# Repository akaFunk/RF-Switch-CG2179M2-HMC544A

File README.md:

# RF Switch CG2179M2 or HMC544A
This PCB can hold either the CEL CG2179M2 [1] or the Analog Devices (former Hitite) HMC544A [2] which are both medium power reflective RF switches (31 and 39 dBm, respectively). The frequency range is DC to 3 GHz or DC to 4 GHz, respectively.

The PCB has a height of 0.6 mm, which is crucial (at least at higher frequencies) and it was ordered in China [3]. The populated PCB was soldered into a tinplate filter housing FG1 of size 37x20x20 mm [4]. To get the control voltages into the housing two 1000 pF feed through capacitor DF 38 [5] were used.

If you wish to use the switch for fast switching you should not populate the two capacitors C4 and C5. Additionally C1, C2 and C3 may be increased for frequencies lower than 100 MHz and decreased for frequencies above 500 MHz. Use proper high frequency capacitors. If DC signal is required, the capacitors C1, C2 and C3 must be replaced by a short or 0 Ohm resistor.

## Images

## References
[1] http://www.cel.com/parts.do?command=load&idRootPart=2604  
[2] http://www.analog.com/en/products/rf-microwave/rf-switches/spdt-t-r/hmc544a.html  
[3] http://www.elecrow.com  
[4] http://www.schubert-gehaeuse.de/prod01.htm  
[5] http://www.oppermann-electronic.de/html/durchf__c_s.html

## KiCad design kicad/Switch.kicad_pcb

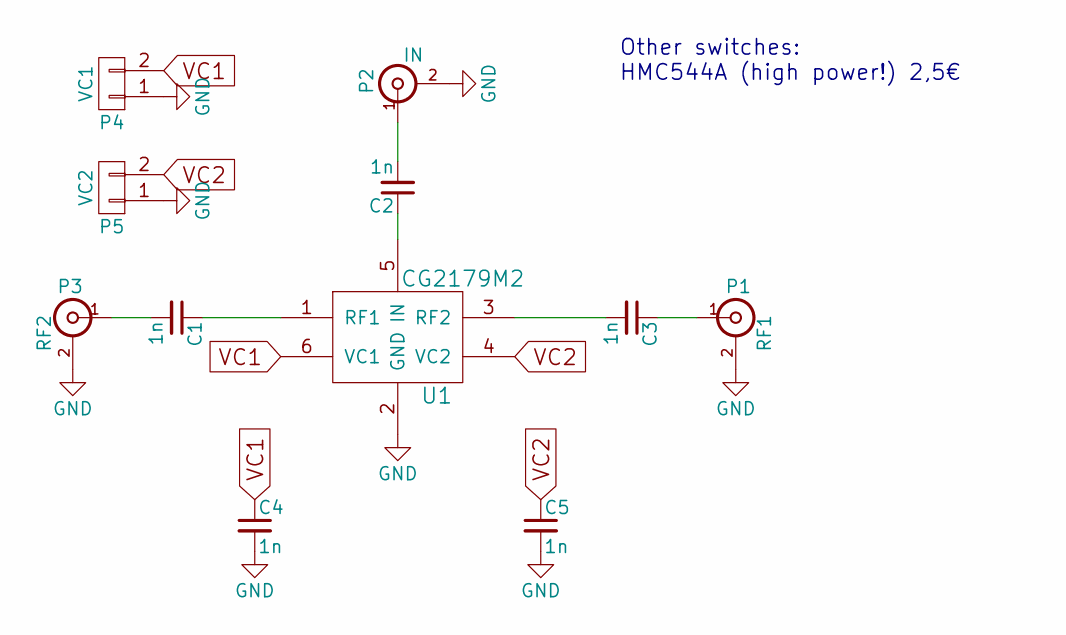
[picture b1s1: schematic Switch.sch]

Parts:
C1, C2, C3, C4, C5: 1n; C_0603_HandSoldering
P1: RF1; CON-SMA-EDGE; MPN 2579819
P2: IN; CON-SMA-EDGE; MPN 2579819
P3: RF2; CON-SMA-EDGE; MPN 2579819
P4: VC1; Pin_Header_Straight_1x02
P5: VC2; Pin_Header_Straight_1x02
U1: CG2179M2; SwitchMulti; MPN CG2179M2-C4

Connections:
GND: C4.2, C5.2, P1.2 (Ext), P2.2 (Ext), P3.2 (Ext), P4.1, P5.1, U1.2 (GND)
unnamed: C1.1, U1.1 (RF1)
unnamed: C1.2, P3.1 (In)
unnamed: C2.1, U1.5 (IN)
unnamed: C2.2, P2.1 (In)
unnamed: C3.1, P1.1 (In)
unnamed: C3.2, U1.3 (RF2)
VC1: C4.1, P4.2, U1.6 (VC1)
VC2: C5.1, P5.2, U1.4 (VC2)

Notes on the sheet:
Other switches: HMC544A (high power!) 2,5€

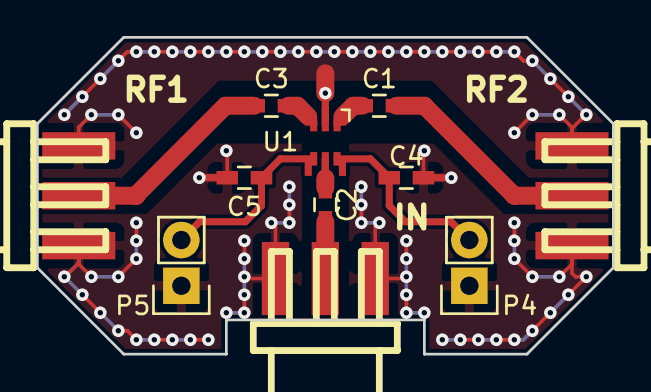
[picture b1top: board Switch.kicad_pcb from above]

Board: 2 copper layers, 32.0 x 17.6 mm, 11 parts (0 on the bottom side), 9 nets.

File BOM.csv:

Reference,Quantity,Value,MPN
P1,1,RF1,2579819
P3,1,RF2,2579819
C1;C3;C2;C5;C4,5,1n,
P2,1,IN,2579819
U1,1,CG2179M2,CG2179M2-C4
P4,1,VC1,
P5,1,VC2,

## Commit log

2018-05-19 Fixed typo
2018-05-19 Added BOM
